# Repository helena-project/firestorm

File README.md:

firestorm
=========

Arduino compatible M4/15.4/BLE combo

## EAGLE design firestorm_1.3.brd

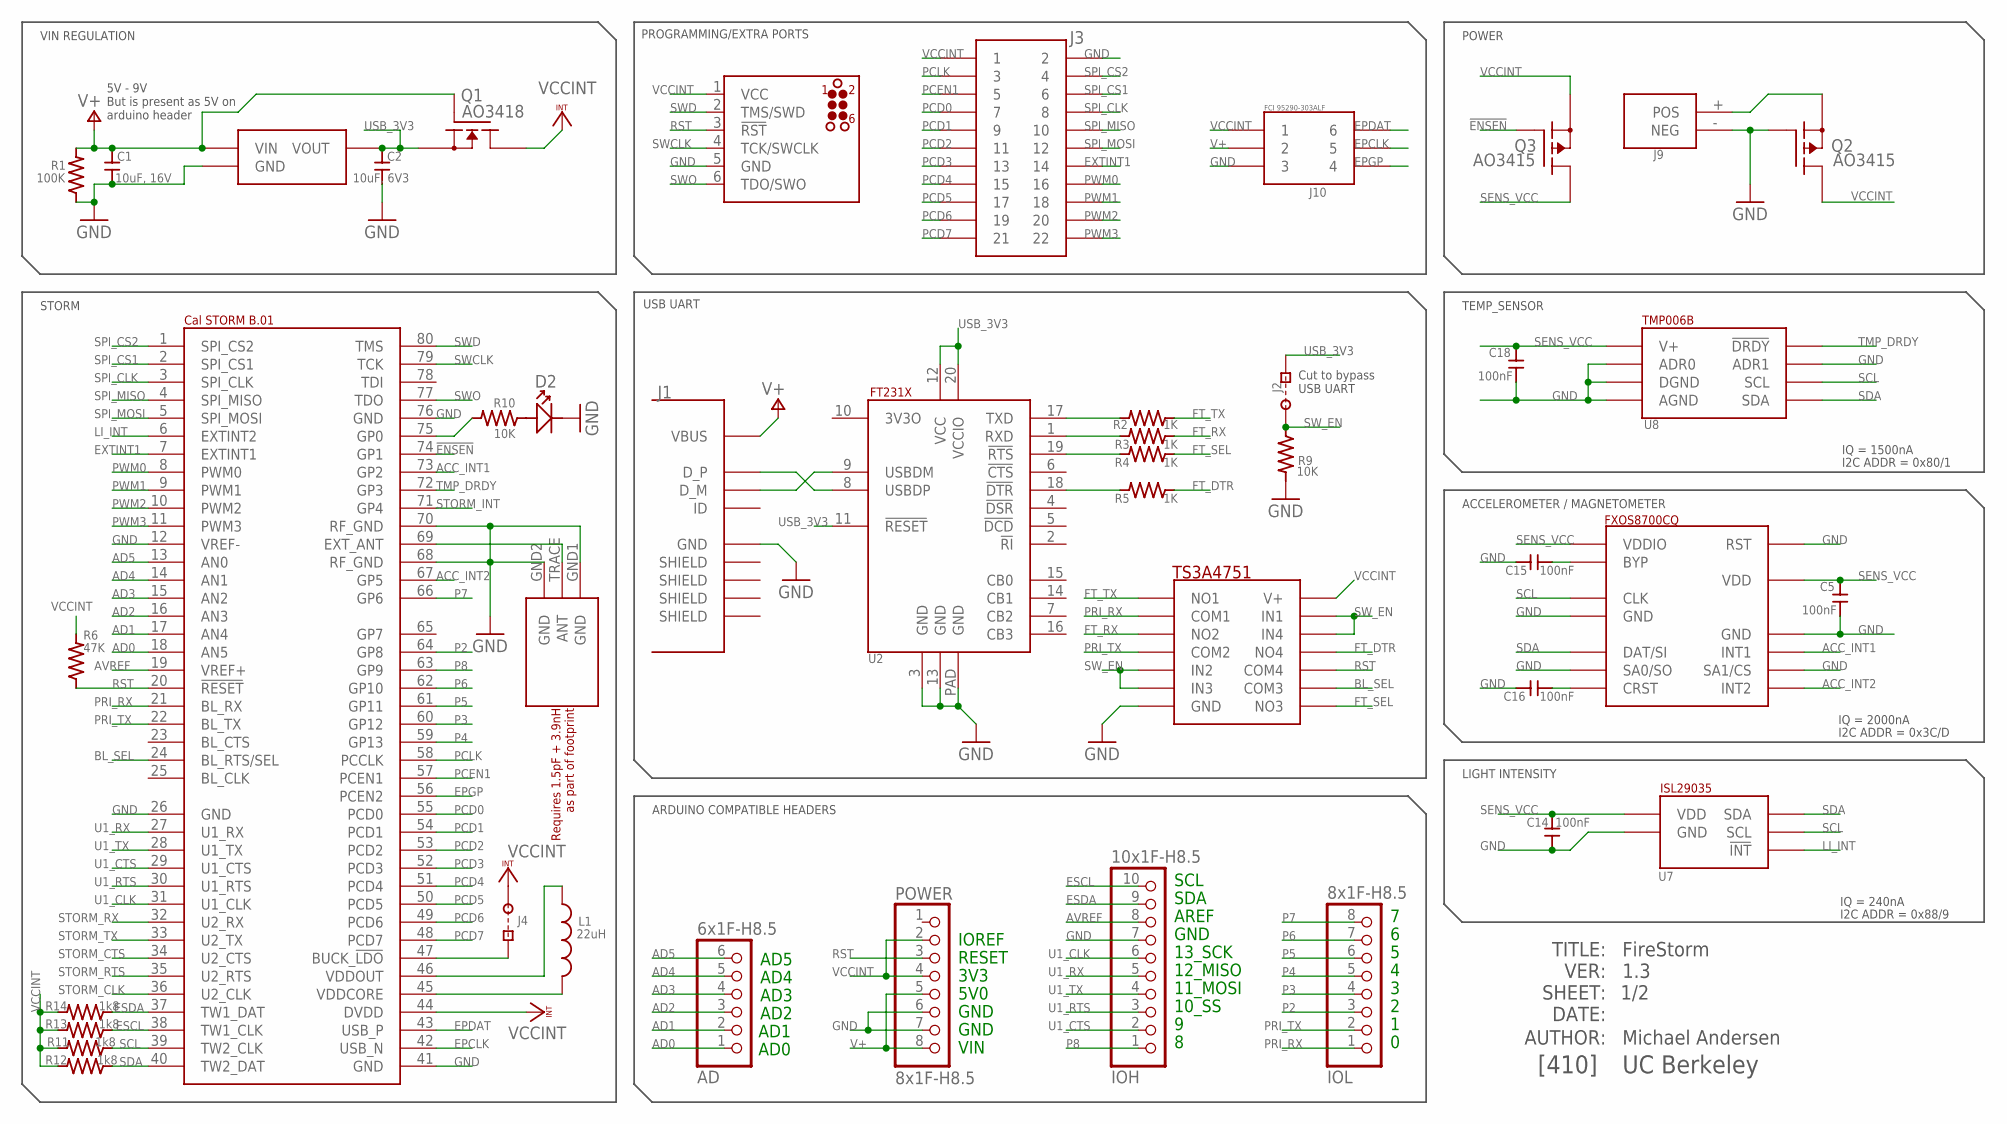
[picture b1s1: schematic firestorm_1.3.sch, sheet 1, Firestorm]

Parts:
AD: 6x1F-H8.5; 1X06
C1: 10uF, 16V; 0805
C2: 10uF, 6V3; C0603
C5, C14, C15, C16, C18: 100nF; C0402
D2: STATLED; LINE_0805
IOH: 10x1F-H8.5; 1X10
IOL: 8x1F-H8.5; 1X08
J1: USBSMT; USB_SMT
J2: CUTJ; CUT
J3: 22WIDC
J4: CUTJBOT; CUT2
J8: JLINK_CONNECT; TC2030-MCP-NL
J9: BATCON
J10: THRUB_POWER; POWER_MODULE
L1: 22uH; SRN4018
POWER: 8x1F-H8.5; 1X08
Q1: AO3418; SOT23
Q2, Q3: AO3415; SOT23
R1: 100K; C0402
R2, R3, R4, R5: 1K; C0402
R6: 47K; C0402
R9, R10: 10K; C0402
R11, R12, R13, R14: 1k8; C0402
U1: STORM_B.01; STORM_LANDING
U2: FT231X; QFN20L
U3: LD1117S33CTR_3V3_REG; SOT223
U4: QUAD_SWITCH_TS3A4751; TSSOP14
U5: ACCEL_FXOS8700CQ; TQFN16
U7: ISL29035
U8: TMP006B; TMP006
U$2: JOHANSON; JOHANSON_ANTENNA

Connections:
!ENSEN!: Q3.1 (G), U1.74 (GP1)
ACCEL_BYP: C15.1, U5.P2 (BYP)
ACC_INT1: U1.73 (GP2), U5.P11 (INT1)
ACC_INT2: U1.67 (GP5), U5.P9 (INT2)
AD0: AD.1, U1.18 (AN5)
AD1: AD.2, U1.17 (AN4)
AD2: AD.3, U1.16 (AN3)
AD3: AD.4, U1.15 (AN2)
AD4: AD.5, U1.14 (AN1)
AD5: AD.6, U1.13 (AN0)
AVREF: IOH.8, U1.19 (VREF+)
BL_SEL: U1.24 (BL_RTS/SEL), U4.9 (COM3)
EPCLK: J10.5, U1.42 (USB_N)
EPDAT: J10.6, U1.43 (USB_P)
EPGP: J10.4, U1.56 (PCEN2)
ESCL: IOH.10, R13.2, U1.38 (TW1_CLK)
ESDA: IOH.9, R14.2, U1.37 (TW1_DAT)
EXTINT1: J3.14, U1.7 (EXTINT1)
FT_DTR: R5.2, U4.11 (NO4)
FT_RX: R3.2, U4.3 (NO2)
FT_SEL: R4.2, U4.8 (NO3)
FT_TX: R2.2, U4.1 (NO1)
GND: C1.1, C2.1, C5.1, C14.1, C15.2, C16.2, C18.1, D2.LINE (-), IOH.7, J1.5GND (GND), J3.2, J8.5 (GND), J9.- (NEG), J10.3, POWER.6, POWER.7, Q2.1 (G), R1.2, R9.1, U1.12 (VREF-), U1.26 (GND), U1.41 (GND), U1.68 (RF_GND), U1.70 (RF_GND), U1.76 (GND), U2.3 (GND), U2.13 (GND), U2.PAD (GND), U3.1 (GND), U4.7 (GND), U5.P5 (GND), U5.P7 (SA0/SO), U5.P10 (SA1/CS), U5.P12 (GND), U5.P16 (RST), U7.2 (GND), U8.A1 (DGND), U8.A2 (AGND), U8.B1 (ADR1), U8.C1 (ADR0), U$2.GND1 (GND), U$2.GND2 (GND); also elsewhere on the board
LI_INT: U1.6 (EXTINT2), U7.4 (!INT!)
unnamed: J1.3D+ (D_P), U2.8 (USBDP)
unnamed: J1.2D- (D_M), U2.9 (USBDM)
unnamed: R2.1, U2.17 (TXD)
unnamed: R3.1, U2.1 (RXD)
unnamed: L1.P$2, U1.45 (VDDCORE)
unnamed: U1.69 (EXT_ANT), U$2.TRACE (ANT)
unnamed: C16.1, U5.P8 (CRST)
unnamed: R4.1, U2.19 (!RTS!)
unnamed: R5.1, U2.18 (!DTR!)
unnamed: L1.P$1, U1.46 (VDDOUT)
unnamed: R10.1, U1.75 (GP0)
unnamed: J4.SQ, U1.47 (BUCK_!LDO!)
unnamed: D2.NOLINE (+), R10.2
unnamed: J9.+ (POS), Q2.2 (S)
P2: IOL.3, U1.64 (GP8)
P3: IOL.4, U1.60 (GP12)
P4: IOL.5, U1.59 (GP13)
P5: IOL.6, U1.61 (GP11)
P6: IOL.7, U1.62 (GP10)
P7: IOL.8, U1.66 (GP6)
P8: IOH.1, U1.63 (GP9)
PCD0: J3.7, U1.55 (PCD0)
PCD1: J3.9, U1.54 (PCD1)
PCD2: J3.11, U1.53 (PCD2)
PCD3: J3.13, U1.52 (PCD3)
PCD4: J3.15, U1.51 (PCD4)
PCD5: J3.17, U1.50 (PCD5)
PCD6: J3.19, U1.49 (PCD6)
PCD7: J3.21, U1.48 (PCD7)
PCEN1: J3.5, U1.57 (PCEN1)
PCLK: J3.3, U1.58 (PCCLK)
PRI_RX: IOL.1, U1.21 (BL_RX), U4.2 (COM1)
PRI_TX: IOL.2, U1.22 (BL_TX), U4.4 (COM2)
PWM0: J3.16, U1.8 (PWM0)
PWM1: J3.18, U1.9 (PWM1)
PWM2: J3.20, U1.10 (PWM2)
PWM3: J3.22, U1.11 (PWM3)
RST: J8.3 (!RST!), POWER.3, R6.2, U1.20 (!RESET!), U4.10 (COM4)
SCL: R11.2, U1.39 (TW2_CLK), U5.P4 (CLK), U7.5 (SCL), U8.B3 (SCL); also elsewhere on the board
SDA: R12.2, U1.40 (TW2_DAT), U5.P6 (DAT/SI), U7.6 (SDA), U8.C3 (SDA); also elsewhere on the board
SENS_VCC: C5.2, C14.2, C18.2, Q3.3 (D), U5.P1 (VDDIO), U5.P14 (VDD), U7.1 (VDD), U8.A3 (V+)
SPI_CLK: J3.8, U1.3 (SPI_CLK)
SPI_CS1: J3.6, U1.2 (SPI_CS1)
SPI_CS2: J3.4, U1.1 (SPI_CS2)
SPI_MISO: J3.10, U1.4 (SPI_MISO)
SPI_MOSI: J3.12, U1.5 (SPI_MOSI)
STORM_CLK: U1.36 (U2_CLK); also elsewhere on the board
STORM_CTS: U1.34 (U2_CTS); also elsewhere on the board
STORM_INT: U1.71 (GP4); also elsewhere on the board
STORM_RTS: U1.35 (U2_RTS); also elsewhere on the board
STORM_RX: U1.32 (U2_RX); also elsewhere on the board
STORM_TX: U1.33 (U2_TX); also elsewhere on the board
SWCLK: J8.4 (TCK/SWCLK), U1.79 (TCK)
SWD: J8.2 (TMS/SWD), U1.80 (TMS)
SWO: J8.6 (TDO/SWO), U1.77 (TDO)
SW_EN: J2.R, R9.2, U4.5 (IN2), U4.6 (IN3), U4.12 (IN4), U4.13 (IN1)
TMP_DRDY: U1.72 (GP3), U8.C2 (!DRDY!)
U1_CLK: IOH.6, U1.31 (U1_CLK)
U1_CTS: IOH.2, U1.29 (U1_CTS)
U1_RTS: IOH.3, U1.30 (U1_RTS)
U1_RX: IOH.5, U1.27 (U1_RX)
U1_TX: IOH.4, U1.28 (U1_TX)
USB_3V3: C2.2, J2.SQ, Q1.2 (S), U2.11 (!RESET!), U2.12 (VCC), U2.20 (VCCIO), U3.2 (VOUT)
V+: C1.2, J1.1VBUS (VBUS), J10.2, POWER.5, POWER.8, Q1.1 (G), R1.1, U3.3 (VIN); also elsewhere on the board
VCCINT: J3.1, J4.R, J8.1 (VCC), J10.1, POWER.2, POWER.4, Q1.3 (D), Q2.3 (D), Q3.2 (S), R6.1, R11.1, R12.1, R13.1, R14.1, U1.44 (DVDD), U4.14 (V+); also elsewhere on the board

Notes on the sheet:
10_SS
11_MOSI
12_MISO
13_SCK
GND
AREF
SDA
SCL
AD0
AD1
AD2
AD3
AD4
AD5
VIN
3V3
RESET
5V0
IOREF
5V - 9V
But is present as 5V on arduino header
ACCELEROMETER / MAGNETOMETER
IQ = 240nA
LIGHT INTENSITY
I2C ADDR = 0x88/9
I2C ADDR = 0x3C/D
IQ = 2000nA
TEMP_SENSOR
I2C ADDR = 0x80/1
IQ = 1500nA
ARDUINO COMPATIBLE HEADERS
VIN REGULATION
Cut to bypass USB UART
USB UART
POWER
STORM
PROGRAMMING/EXTRA PORTS
TITLE:
VER:
DATE:

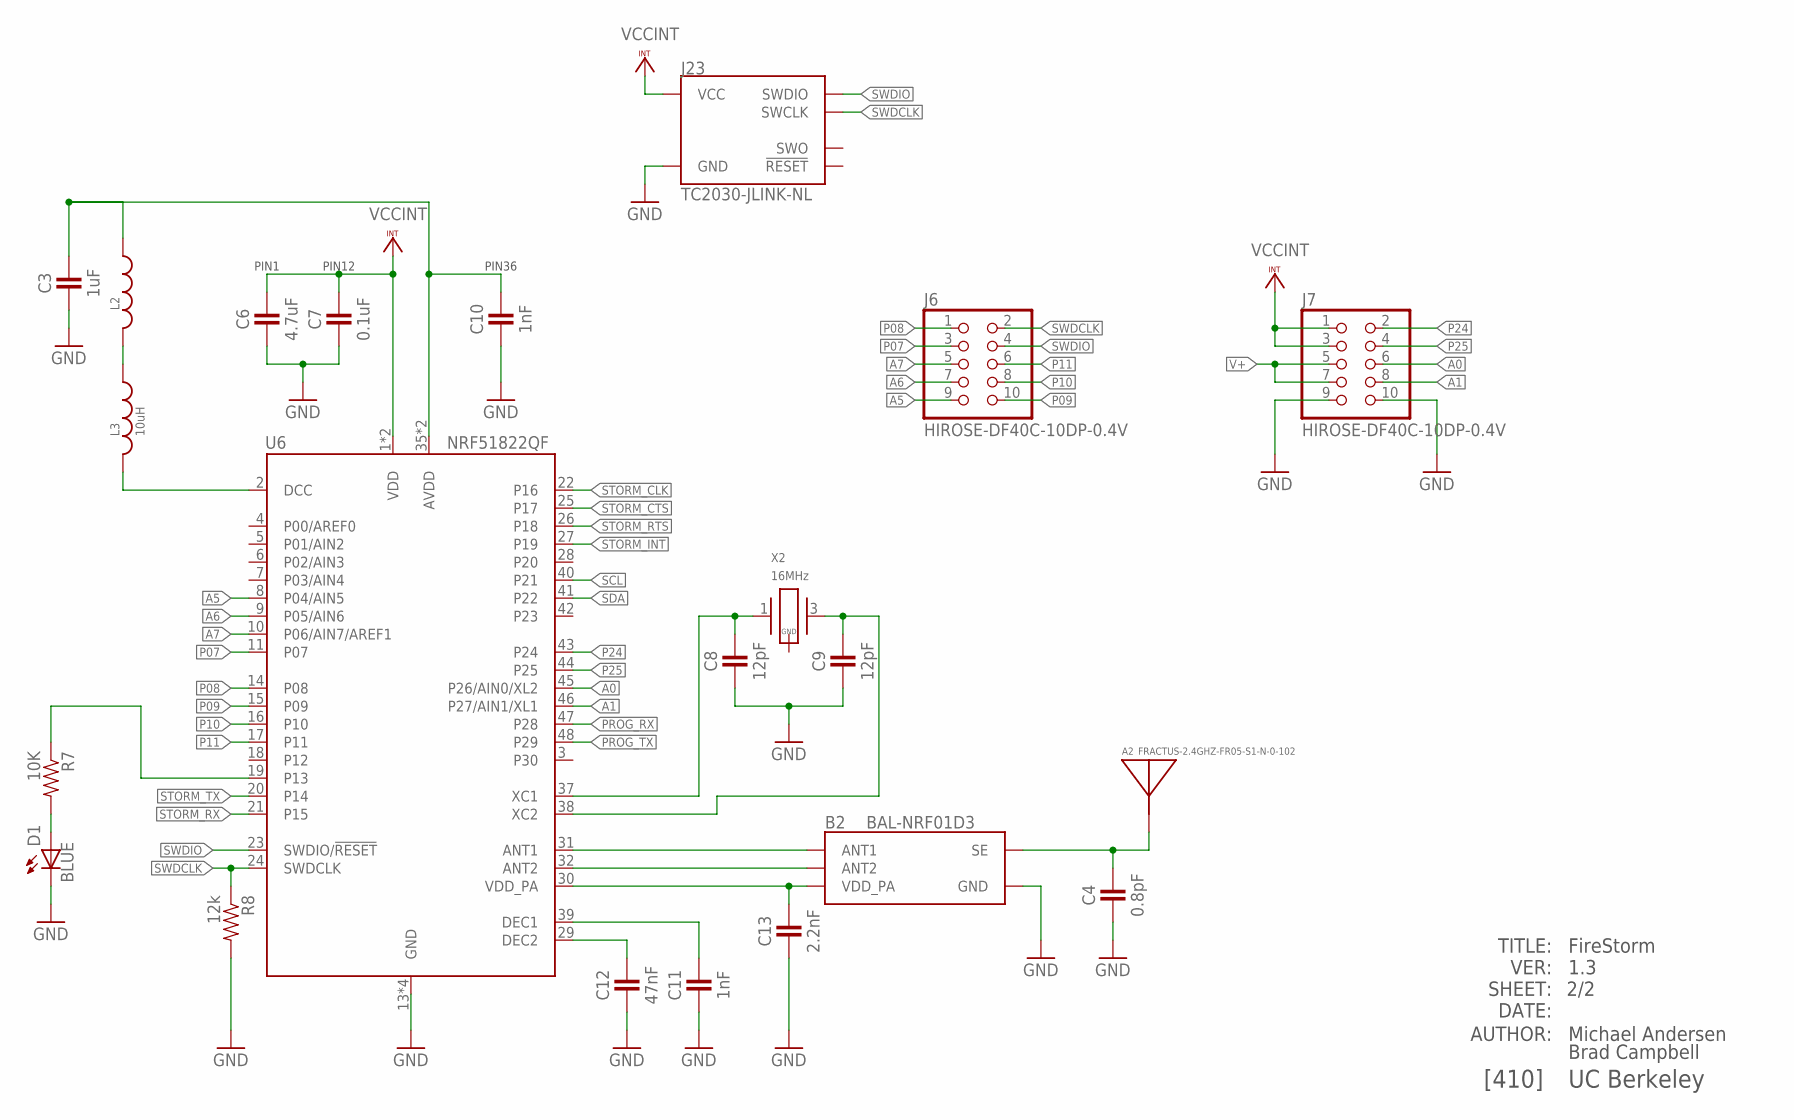
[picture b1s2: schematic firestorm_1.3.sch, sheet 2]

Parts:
A2: FRACTUS-2.4GHZ-FR05-S1-N-0-102; FRACTUS-ANTENNA-FR05-S1-N-0-102
B2: BAL-NRF01D3
C3: 1uF; 0402_CAP; DIGIKEY 1276-1513-1-ND
C4: 0.8pF; 0402_CAP; DIGIKEY 490-5419-1-ND
C6: 4.7uF; 0402_CAP; DIGIKEY 445-5947-1-ND
C7: 0.1uF; 0402_CAP; DIGIKEY 445-4952-1-ND
C8, C9: 12pF; 0402_CAP; DIGIKEY 490-6197-1-ND
C10, C11: 1nF; 0402_CAP; DIGIKEY 490-1303-1-ND
C12: 47nF; 0402_CAP; DIGIKEY 445-1264-1-ND
C13: 2.2nF; 0402_CAP; DIGIKEY 490-5419-1-ND
D1: BLUE; LED-0603
J6, J7: HIROSE-DF40C-10DP-0.4V; 2X5/SMD/0.4MM
J23: TC2030-JLINK-NL; TC2030-IDC-NL
L2: INDUCTOR0402; 0402_CAP; DIGIKEY 587-1521-1-ND
L3: 10uH; 0603_CAP; DIGIKEY 490-4025-1-ND
R7: 10K; 0402_RES; DIGIKEY RHM470CECT-ND
R8: 12k; 0402_RES; DIGIKEY RHM12.0KCDCT-ND
U6: NRF51822QF; QFN-48-6MM
X2: 16MHz; TXC-8Y; DIGIKEY 887-2003-1-ND

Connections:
A0: J7.6, U6.45 (P26/AIN0/XL2)
A1: J7.8, U6.46 (P27/AIN1/XL1)
A5: J6.9, U6.8 (P04/AIN5)
A6: J6.7, U6.9 (P05/AIN6)
A7: J6.5, U6.10 (P06/AIN7/AREF1)
AVDD: C3.1, C10.1, L2.1, U6.35 (AVDD), U6.36 (AVDD)
DCC: L3.2, U6.2 (DCC)
GND: B2.GND, C3.2, C4.2, C6.2, C7.2, C8.2, C9.2, C10.2, C11.2, C12.2, C13.2, D1.C, J7.9, J7.10, J23.5 (GND), R8.2, U6.13 (GND), U6.33 (GND), U6.34 (GND), U6.GND; also elsewhere on the board
unnamed: B2.ANT1, U6.31 (ANT1)
unnamed: B2.ANT2, U6.32 (ANT2)
unnamed: A2.1, B2.SE, C4.1
unnamed: C9.1, U6.38 (XC2), X2.3 (2)
unnamed: C11.1, U6.39 (DEC1)
unnamed: R7.1, U6.19 (P13)
unnamed: L2.2, L3.1
unnamed: C8.1, U6.37 (XC1), X2.1
unnamed: C12.1, U6.29 (DEC2)
unnamed: D1.A, R7.2
P07: J6.3, U6.11 (P07)
P08: J6.1, U6.14 (P08)
P09: J6.10, U6.15 (P09)
P10: J6.8, U6.16 (P10)
P11: J6.6, U6.17 (P11)
P24: J7.2, U6.43 (P24)
P25: J7.4, U6.44 (P25)
PROG_RX: U6.47 (P28)
PROG_TX: U6.48 (P29)
SCL: U6.40 (P21); also elsewhere on the board
SDA: U6.41 (P22); also elsewhere on the board
STORM_CLK: U6.22 (P16); also elsewhere on the board
STORM_CTS: U6.25 (P17); also elsewhere on the board
STORM_INT: U6.27 (P19); also elsewhere on the board
STORM_RTS: U6.26 (P18); also elsewhere on the board
STORM_RX: U6.21 (P15); also elsewhere on the board
STORM_TX: U6.20 (P14); also elsewhere on the board
SWDCLK: J6.2, J23.4 (SWCLK), R8.1, U6.24 (SWDCLK)
SWDIO: J6.4, J23.2 (SWDIO), U6.23 (SWDIO/!RESET)
V+: J7.5, J7.7; also elsewhere on the board
VCCINT: C6.1, C7.1, J7.1, J7.3, J23.1 (VCC), U6.1 (VDD), U6.12 (VDD); also elsewhere on the board
VDD_PA: B2.VCC (VDD_PA), C13.1, U6.30 (VDD_PA)

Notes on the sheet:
PIN12
PIN1
PIN36
TITLE:
VER:
DATE:
AUTHOR:
FireStorm
1.3
Michael Andersen
[410]
UC Berkeley
SHEET:
Brad Campbell

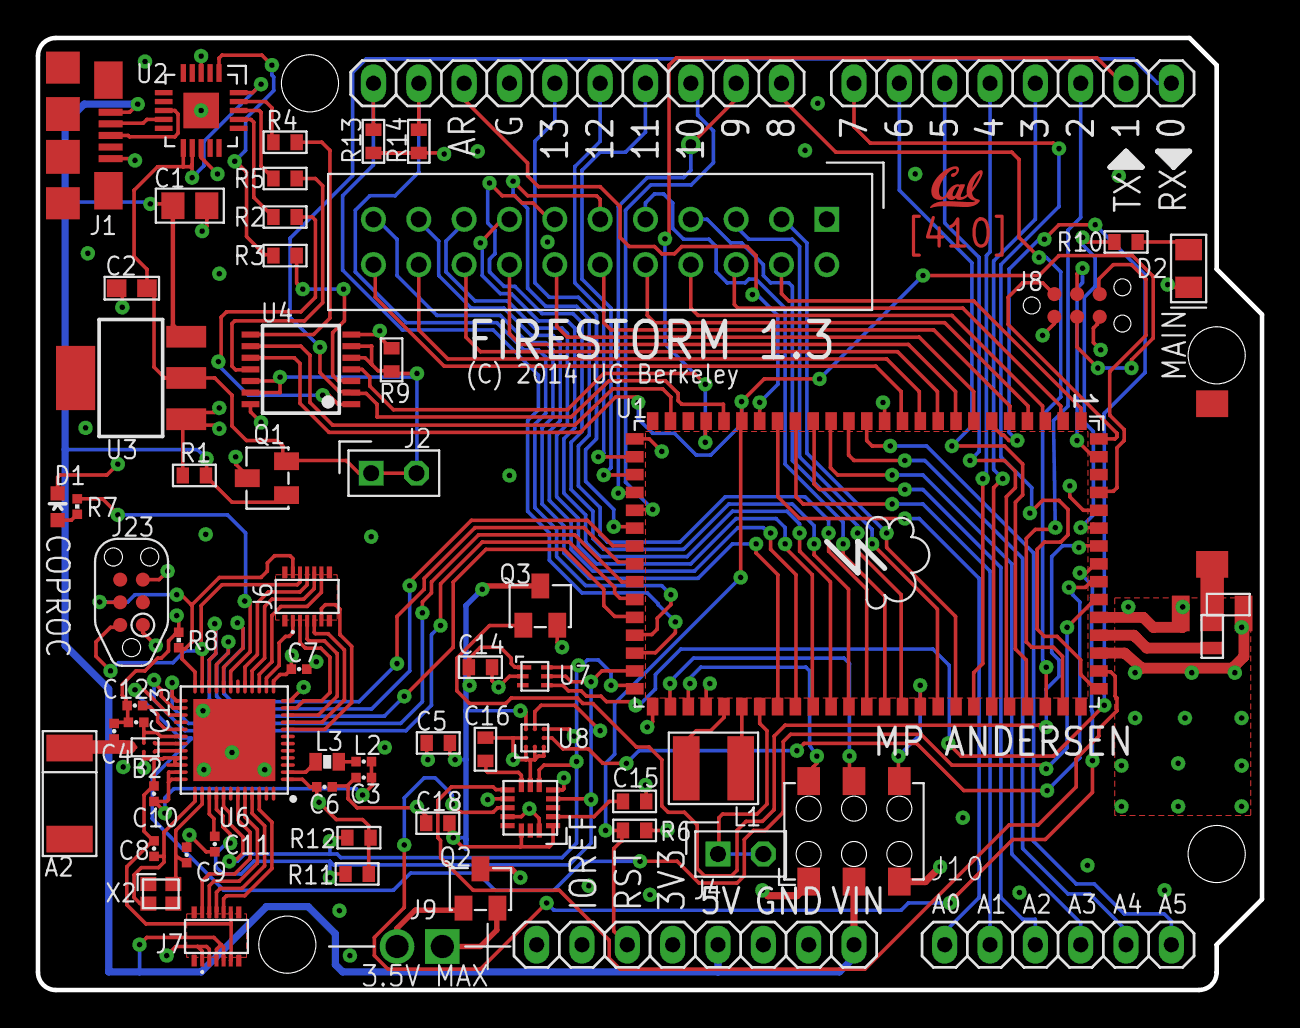
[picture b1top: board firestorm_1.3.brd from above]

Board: 4 copper layers, 68.6 x 53.3 mm, 66 parts (0 on the bottom side), 116 nets.

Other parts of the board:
U$1: BEAR

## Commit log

2014-10-02 Add version 1.1
2015-01-22 Add 1.3 schematic
2015-02-27 Add eagle files for board

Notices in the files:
firestorm_1.3.brd:
(C) 2014 UC Berkeley
parts and their libraries:
storm: ©2009 ROFA.cz
SparkFun-LED: Licensing: CC v3.0 Share-Alike You are welcome to use this library for commercial purposes.
